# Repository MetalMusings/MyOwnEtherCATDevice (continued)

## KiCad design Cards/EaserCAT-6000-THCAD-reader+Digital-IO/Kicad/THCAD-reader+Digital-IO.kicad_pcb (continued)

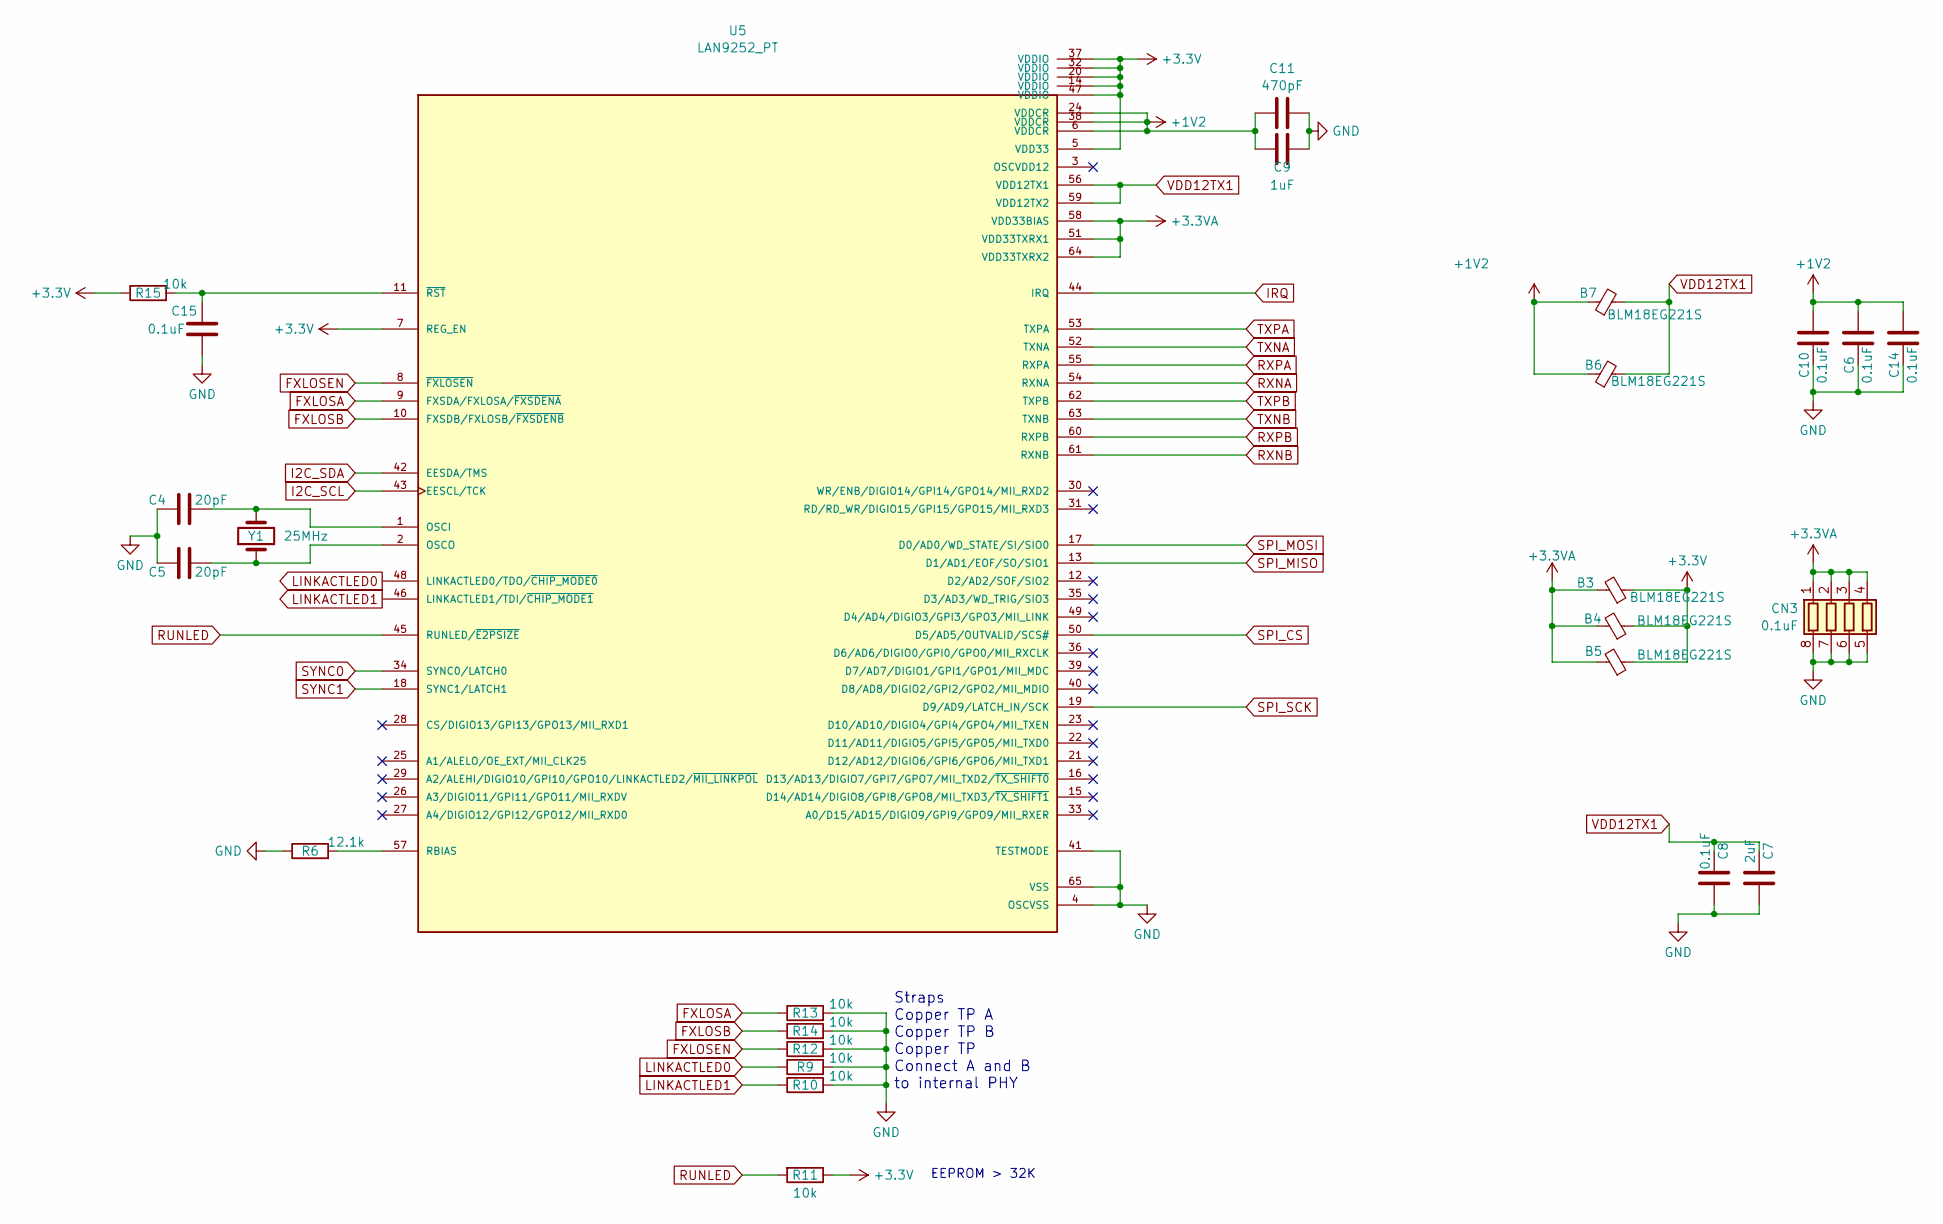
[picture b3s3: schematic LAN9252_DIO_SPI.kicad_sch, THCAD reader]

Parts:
B3, B4, B5, B6, B7: BLM18EG221S; C_0805_2012Metric
C4, C5: 20pF; C_0603_1608Metric
C6, C8, C10, C14, C15: 0.1uF; C_0603_1608Metric
C7: 2uF; C_0603_1608Metric
C9: 1uF; C_0603_1608Metric
C11: 470pF; C_0603_1608Metric
CN3: 0.1uF; R_Array_Convex_4x0603
R6: 12.1k; R_0603_1608Metric
R9, R10, R11, R12, R13, R14, R15: 10k; R_0603_1608Metric
U5: LAN9252_PT; TQFP-64-1EP_10x10mm_P0.5mm_EP8x8mm; PARTREV 04-08-15
Y1: 25MHz; Crystal_HC49-4H_Vertical

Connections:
+1V2: B6.1, B7.1, C6.2, C9.1, C10.2, C11.1, C14.2, U5.6 (VDDCR), U5.24 (VDDCR), U5.38 (VDDCR)
+3.3V: B3.1, B4.1, B5.1, R11.1, R15.1, U5.5 (VDD33), U5.7 (REG_EN), U5.14 (VDDIO), U5.20 (VDDIO), U5.32 (VDDIO), U5.37 (VDDIO), U5.47 (VDDIO); also elsewhere on the board
+3.3VA: B3.2, B4.2, B5.2, CN3.1 (R1.1), CN3.2 (R2.1), CN3.3 (R3.1), CN3.4 (R4.1), U5.51 (VDD33TXRX1), U5.58 (VDD33BIAS), U5.64 (VDD33TXRX2)
FXLOSA: R13.1, U5.9 (FXSDA/FXLOSA/~FXSDENA)
FXLOSB: R14.1, U5.10 (FXSDB/FXLOSB/~FXSDENB)
FXLOSEN: R12.1, U5.8 (~FXLOSEN)
GND: C4.1, C5.1, C6.1, C7.2, C8.2, C9.2, C10.1, C11.2, C14.1, C15.1, CN3.5 (R4.2), CN3.6 (R3.2), CN3.7 (R2.2), CN3.8 (R1.2), R6.1, R9.2, R10.2, R12.2, R13.2, R14.2, U5.4 (OSCVSS), U5.41 (TESTMODE), U5.65 (VSS); also elsewhere on the board
I2C_SCL: U5.43 (EESCL/TCK); also elsewhere on the board
I2C_SDA: U5.42 (EESDA/TMS); also elsewhere on the board
IRQ: U5.44 (IRQ); also elsewhere on the board
LINKACTLED0: R9.1, U5.48 (LINKACTLED0/TDO/~CHIP_MODE0); also elsewhere on the board
LINKACTLED1: R10.1, U5.46 (LINKACTLED1/TDI/~CHIP_MODE1); also elsewhere on the board
unnamed: C4.2, U5.1 (OSCI), Y1.2
unnamed: C5.2, U5.2 (OSCO), Y1.1
unnamed: R6.2, U5.57 (RBIAS)
unnamed: C15.2, R15.2, U5.11 (~RST)
RUNLED: R11.2, U5.45 (RUNLED/~E2PSIZE); also elsewhere on the board
RXNA: U5.54 (RXNA); also elsewhere on the board
RXNB: U5.61 (RXNB); also elsewhere on the board
RXPA: U5.55 (RXPA); also elsewhere on the board
RXPB: U5.60 (RXPB); also elsewhere on the board
SPI_CS: U5.50 (D5/AD5/OUTVALID/SCS#); also elsewhere on the board
SPI_MISO: U5.13 (D1/AD1/EOF/SO/SIO1); also elsewhere on the board
SPI_MOSI: U5.17 (D0/AD0/WD_STATE/SI/SIO0); also elsewhere on the board
SPI_SCK: U5.19 (D9/AD9/LATCH_IN/SCK); also elsewhere on the board
SYNC0: U5.34 (SYNC0/LATCH0); also elsewhere on the board
SYNC1: U5.18 (SYNC1/LATCH1); also elsewhere on the board
TXNA: U5.52 (TXNA); also elsewhere on the board
TXNB: U5.63 (TXNB); also elsewhere on the board
TXPA: U5.53 (TXPA); also elsewhere on the board
TXPB: U5.62 (TXPB); also elsewhere on the board
VDD12TX1: B6.2, B7.2, C7.1, C8.1, U5.56 (VDD12TX1), U5.59 (VDD12TX2)

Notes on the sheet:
Straps Copper TP A Copper TP B Copper TP Connect A and B to internal PHY
EEPROM > 32K

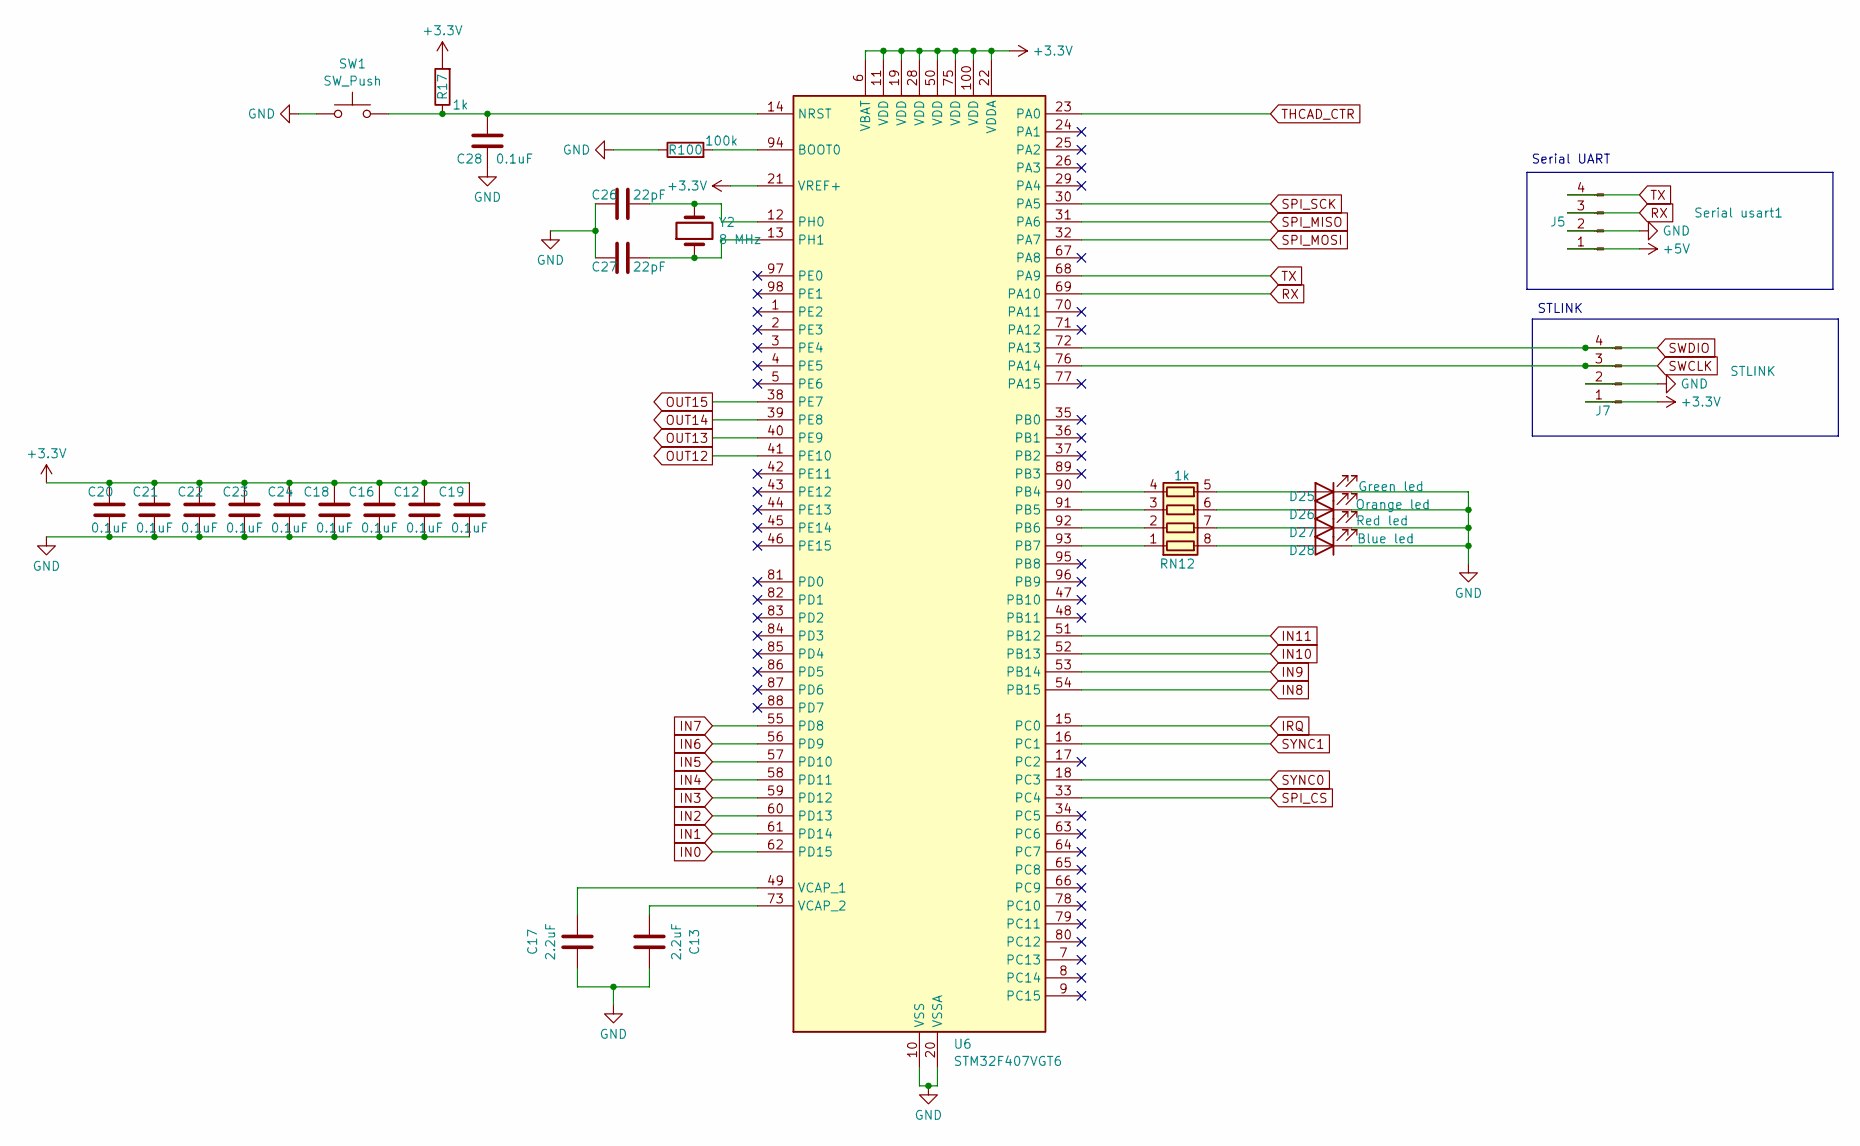
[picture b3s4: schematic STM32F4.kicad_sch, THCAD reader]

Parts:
C12, C16, C18, C19, C20, C21, C22, C23, C24, C28: 0.1uF; C_0603_1608Metric
C13, C17: 2.2uF; C_0603_1608Metric
C26, C27: 22pF; C_0603_1608Metric
D25: Green led; LED_0603_1608Metric
D26: Orange led; LED_0603_1608Metric
D27: Red led; LED_0603_1608Metric
D28: Blue led; LED_0603_1608Metric
J5: Serial usart1; JST_XH_B4B-XH-A_1x04_P2.50mm_Vertical
J7: STLINK; JST_XH_B4B-XH-A_1x04_P2.50mm_Vertical
R17: 1k; R_0603_1608Metric
R100: 100k; R_0603_1608Metric
RN12: 1k; R_Array_Convex_4x0603
SW1: SW_Push; SW_Push_1P1T_XKB_TS-1187A
U6: STM32F407VGT6; LQFP-100_14x14mm_P0.5mm
Y2: 8 MHz; Crystal_HC49-4H_Vertical

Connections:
+3.3V: C12.1, C16.1, C18.1, C19.1, C20.1, C21.1, C22.1, C23.1, C24.1, J7.1, R17.2, U6.6 (VBAT), U6.11 (VDD), U6.19 (VDD), U6.21 (VREF+), U6.22 (VDDA), U6.28 (VDD), U6.50 (VDD), U6.75 (VDD), U6.100 (VDD); also elsewhere on the board
+5V: J5.1; also elsewhere on the board
GND: C12.2, C13.1, C16.2, C17.1, C18.2, C19.2, C20.2, C21.2, C22.2, C23.2, C24.2, C26.1, C27.1, C28.1, D25.1 (K), D26.1 (K), D27.1 (K), D28.1 (K), J5.2, J7.2, R100.1, SW1.1, U6.10 (VSS), U6.20 (VSSA), U6.27 (VSS), U6.74 (VSS), U6.99 (VSS); also elsewhere on the board
IN0: U6.62 (PD15); also elsewhere on the board
IN1: U6.61 (PD14); also elsewhere on the board
IN2: U6.60 (PD13); also elsewhere on the board
IN3: U6.59 (PD12); also elsewhere on the board
IN4: U6.58 (PD11); also elsewhere on the board
IN5: U6.57 (PD10); also elsewhere on the board
IN6: U6.56 (PD9); also elsewhere on the board
IN7: U6.55 (PD8); also elsewhere on the board
IN8: U6.54 (PB15); also elsewhere on the board
IN9: U6.53 (PB14); also elsewhere on the board
IN10: U6.52 (PB13); also elsewhere on the board
IN11: U6.51 (PB12); also elsewhere on the board
IRQ: U6.15 (PC0); also elsewhere on the board
unnamed: D25.2 (A), RN12.5 (R4.2)
unnamed: D26.2 (A), RN12.6 (R3.2)
unnamed: D27.2 (A), RN12.7 (R2.2)
unnamed: D28.2 (A), RN12.8 (R1.2)
unnamed: RN12.1 (R1.1), U6.93 (PB7)
unnamed: RN12.2 (R2.1), U6.92 (PB6)
unnamed: RN12.3 (R3.1), U6.91 (PB5)
unnamed: RN12.4 (R4.1), U6.90 (PB4)
unnamed: R100.2, U6.94 (BOOT0)
unnamed: C28.2, R17.1, SW1.2, U6.14 (NRST)
unnamed: C26.2, U6.12 (PH0), Y2.2
unnamed: C27.2, U6.13 (PH1), Y2.1
unnamed: C17.2, U6.49 (VCAP_1)
unnamed: C13.2, U6.73 (VCAP_2)
OUT12: U6.41 (PE10); also elsewhere on the board
OUT13: U6.40 (PE9); also elsewhere on the board
OUT14: U6.39 (PE8); also elsewhere on the board
OUT15: U6.38 (PE7); also elsewhere on the board
RX: J5.3, U6.69 (PA10)
SPI_CS: U6.33 (PC4); also elsewhere on the board
SPI_MISO: U6.31 (PA6); also elsewhere on the board
SPI_MOSI: U6.32 (PA7); also elsewhere on the board
SPI_SCK: U6.30 (PA5); also elsewhere on the board
SWCLK: J7.3, U6.76 (PA14)
SWDIO: J7.4, U6.72 (PA13)
SYNC0: U6.18 (PC3); also elsewhere on the board
SYNC1: U6.16 (PC1); also elsewhere on the board
THCAD_CTR: U6.23 (PA0); also elsewhere on the board
TX: J5.4, U6.68 (PA9)

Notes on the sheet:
STLINK
Serial UART

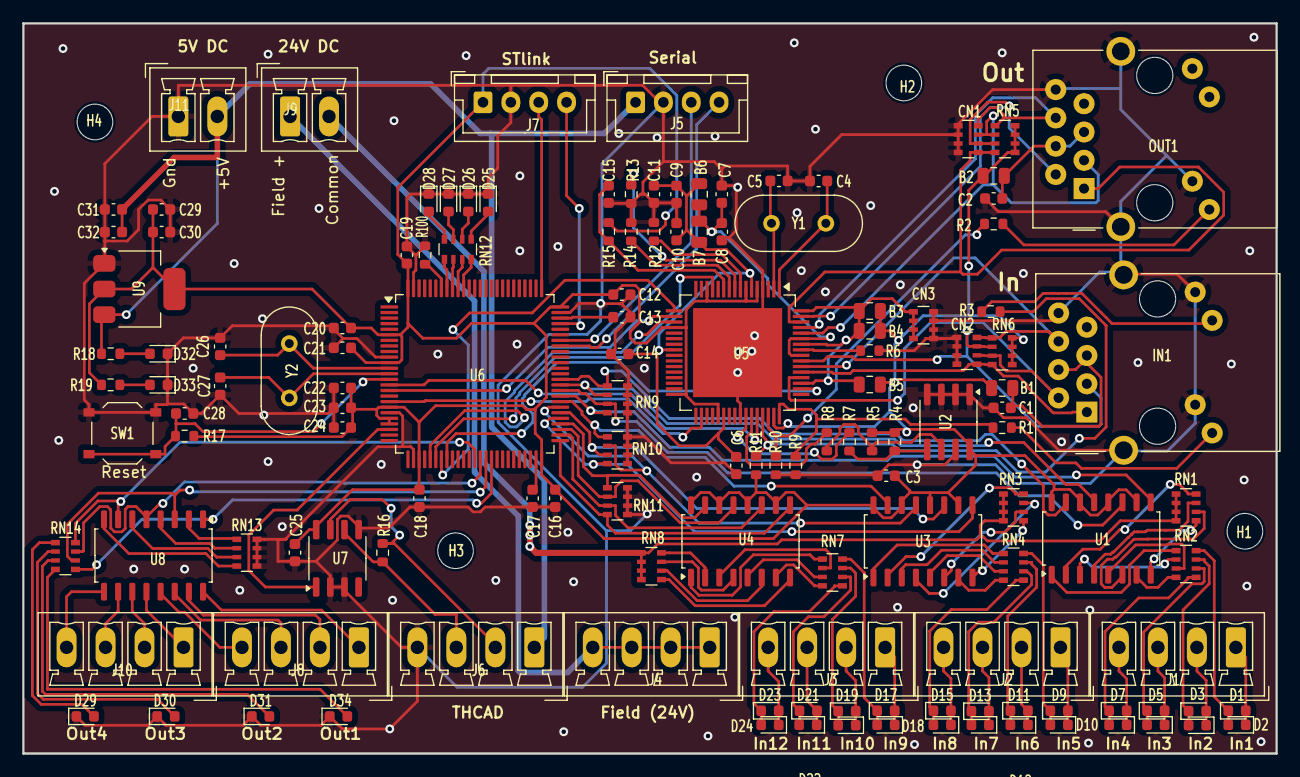
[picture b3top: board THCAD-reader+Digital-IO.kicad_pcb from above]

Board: 2 copper layers, 112.5 x 65.6 mm, 139 parts (0 on the bottom side), 145 nets.

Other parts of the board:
C25: 0.1uF; C_0603_1608Metric
J6: THCAD; PhoenixContact_MCV_1,5_4-G-3.5_1x04_P3.50mm_Vertical
R16: 120; R_0603_1608Metric
U7: MAX3485CSA/ESA; SO-8_3.9x4.9mm_P1.27mm

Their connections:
+3.3V: C25.1, U7.8 (VCC); also elsewhere on the board
+5V: J6.1; also elsewhere on the board
A: J6.2, R16.2, U7.7 (B)
B: J6.3, R16.1, U7.6 (A)
GND: C25.2, J6.4, U7.2 (~RE), U7.3 (DE), U7.5 (GND); also elsewhere on the board
THCAD_CTR: U7.1 (RO); also elsewhere on the board

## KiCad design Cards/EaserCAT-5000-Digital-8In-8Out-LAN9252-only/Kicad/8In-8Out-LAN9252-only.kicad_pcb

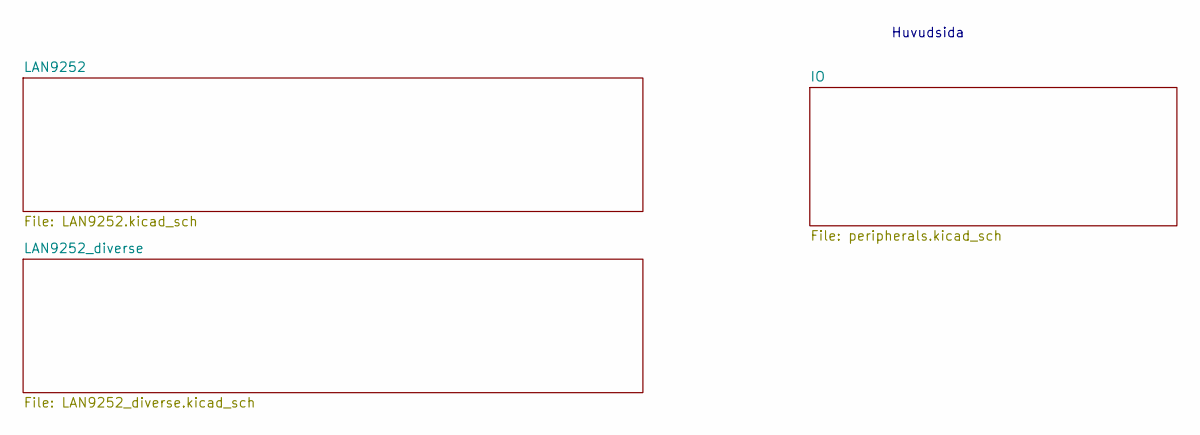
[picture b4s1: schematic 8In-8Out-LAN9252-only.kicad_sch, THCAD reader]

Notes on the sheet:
Huvudsida

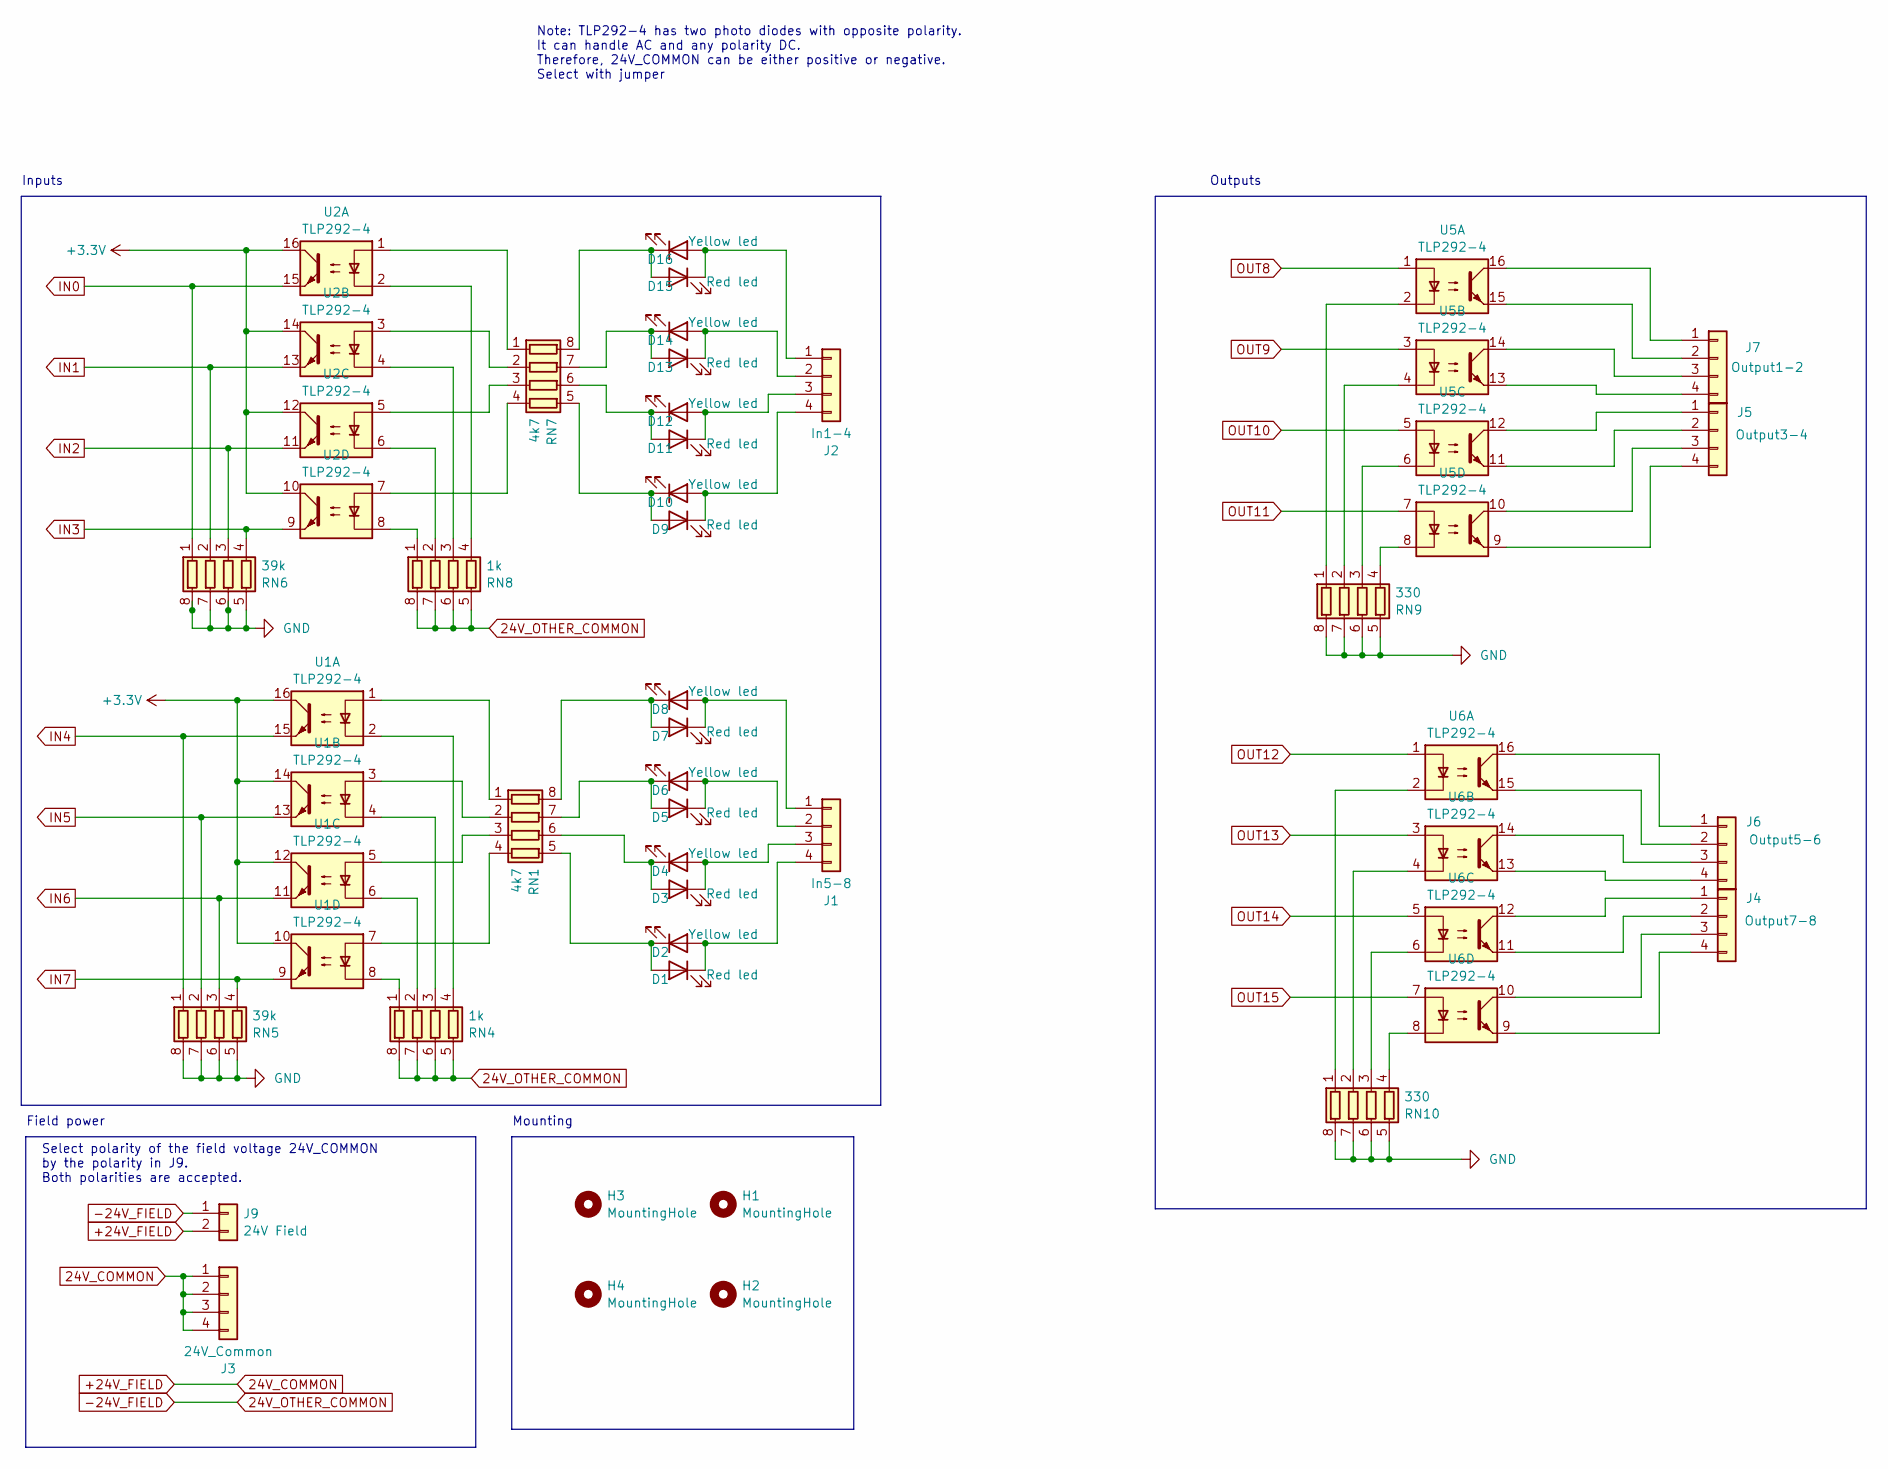
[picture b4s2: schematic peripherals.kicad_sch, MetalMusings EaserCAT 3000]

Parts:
D1, D3, D5, D7, D9, D11, D13, D15: Red led; LED_0603_1608Metric
D2, D4, D6, D8, D10, D12, D14, D16: Yellow led; LED_0603_1608Metric
H1, H2, H3, H4: MountingHole; MountingHole_3.2mm_M3_ISO14580
J1: In5-8; PhoenixContact_MCV_1,5_4-G-3.5_1x04_P3.50mm_Vertical
J2: In1-4; PhoenixContact_MCV_1,5_4-G-3.5_1x04_P3.50mm_Vertical
J3: 24V_Common; PhoenixContact_MCV_1,5_4-G-3.5_1x04_P3.50mm_Vertical
J4: Output7-8; PhoenixContact_MCV_1,5_4-G-3.5_1x04_P3.50mm_Vertical
J5: Output3-4; PhoenixContact_MCV_1,5_4-G-3.5_1x04_P3.50mm_Vertical
J6: Output5-6; PhoenixContact_MCV_1,5_4-G-3.5_1x04_P3.50mm_Vertical
J7: Output1-2; PhoenixContact_MCV_1,5_4-G-3.5_1x04_P3.50mm_Vertical
J9: 24V Field; PhoenixContact_MCV_1,5_2-G-3.5_1x02_P3.50mm_Vertical
RN1, RN7: 4k7; R_Array_Convex_4x0603
RN4, RN8: 1k; R_Array_Convex_4x0603
RN5, RN6: 39k; R_Array_Convex_4x0603
RN9, RN10: 330; R_Array_Convex_4x0603
U1, U2, U5, U6: TLP292-4; SOIC-16_4.55x10.3mm_P1.27mm

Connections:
+3.3V: U1.10, U1.12, U1.14, U1.16, U2.10, U2.12, U2.14, U2.16; also elsewhere on the board
+24V_FIELD: J3.1, J3.2, J3.3, J3.4, J9.2
-24V_FIELD: J9.1, RN4.5 (R4.2), RN4.6 (R3.2), RN4.7 (R2.2), RN4.8 (R1.2), RN8.5 (R4.2), RN8.6 (R3.2), RN8.7 (R2.2), RN8.8 (R1.2)
GND: RN5.5 (R4.2), RN5.6 (R3.2), RN5.7 (R2.2), RN5.8 (R1.2), RN6.5 (R4.2), RN6.6 (R3.2), RN6.7 (R2.2), RN6.8 (R1.2), RN9.5 (R4.2), RN9.6 (R3.2), RN9.7 (R2.2), RN9.8 (R1.2), RN10.5 (R4.2), RN10.6 (R3.2), RN10.7 (R2.2), RN10.8 (R1.2); also elsewhere on the board
IN0: RN6.1 (R1.1), U2.15; also elsewhere on the board
IN1: RN6.2 (R2.1), U2.13; also elsewhere on the board
IN2: RN6.3 (R3.1), U2.11; also elsewhere on the board
IN3: RN6.4 (R4.1), U2.9; also elsewhere on the board
IN4: RN5.1 (R1.1), U1.15; also elsewhere on the board
IN5: RN5.2 (R2.1), U1.13; also elsewhere on the board
IN6: RN5.3 (R3.1), U1.11; also elsewhere on the board
IN7: RN5.4 (R4.1), U1.9; also elsewhere on the board
unnamed: D1.2 (A), D2.1 (K), RN1.5 (R4.2)
unnamed: D1.1 (K), D2.2 (A), J1.4
unnamed: D3.2 (A), D4.1 (K), RN1.6 (R3.2)
unnamed: D3.1 (K), D4.2 (A), J1.3
unnamed: D5.2 (A), D6.1 (K), RN1.7 (R2.2)
unnamed: D5.1 (K), D6.2 (A), J1.2
unnamed: D7.2 (A), D8.1 (K), RN1.8 (R1.2)
unnamed: D7.1 (K), D8.2 (A), J1.1
unnamed: D9.1 (K), D10.2 (A), J2.4
unnamed: D9.2 (A), D10.1 (K), RN7.5 (R4.2)
unnamed: D11.2 (A), D12.1 (K), RN7.6 (R3.2)
unnamed: D11.1 (K), D12.2 (A), J2.3
unnamed: D13.2 (A), D14.1 (K), RN7.7 (R2.2)
unnamed: D13.1 (K), D14.2 (A), J2.2
unnamed: D15.2 (A), D16.1 (K), RN7.8 (R1.2)
unnamed: D15.1 (K), D16.2 (A), J2.1
unnamed: J4.1, U6.12
unnamed: J4.2, U6.11
unnamed: J4.3, U6.10
unnamed: J4.4, U6.9
unnamed: J5.1, U5.12
unnamed: J5.2, U5.11
unnamed: J5.3, U5.10
unnamed: J5.4, U5.9
unnamed: J6.1, U6.16
unnamed: J6.2, U6.15
unnamed: J6.3, U6.14
unnamed: J6.4, U6.13
unnamed: J7.1, U5.16
unnamed: J7.2, U5.15
unnamed: J7.3, U5.14
unnamed: J7.4, U5.13
unnamed: RN1.1 (R1.1), U1.1
unnamed: RN1.2 (R2.1), U1.3
unnamed: RN1.3 (R3.1), U1.5
unnamed: RN1.4 (R4.1), U1.7
unnamed: RN4.1 (R1.1), U1.8
unnamed: RN4.2 (R2.1), U1.6
unnamed: RN4.3 (R3.1), U1.4
unnamed: RN4.4 (R4.1), U1.2
unnamed: RN7.1 (R1.1), U2.1
unnamed: RN7.2 (R2.1), U2.3
unnamed: RN7.3 (R3.1), U2.5
unnamed: RN7.4 (R4.1), U2.7
unnamed: RN8.1 (R1.1), U2.8
unnamed: RN8.2 (R2.1), U2.6
unnamed: RN8.3 (R3.1), U2.4
unnamed: RN8.4 (R4.1), U2.2
unnamed: RN9.1 (R1.1), U5.2
unnamed: RN9.2 (R2.1), U5.4
unnamed: RN9.3 (R3.1), U5.6
unnamed: RN9.4 (R4.1), U5.8
unnamed: RN10.1 (R1.1), U6.2
unnamed: RN10.2 (R2.1), U6.4
unnamed: RN10.3 (R3.1), U6.6
unnamed: RN10.4 (R4.1), U6.8
OUT8: U5.1; also elsewhere on the board
OUT9: U5.3; also elsewhere on the board
OUT10: U5.5; also elsewhere on the board
OUT11: U5.7; also elsewhere on the board
OUT12: U6.1; also elsewhere on the board
OUT13: U6.3; also elsewhere on the board
OUT14: U6.5; also elsewhere on the board
OUT15: U6.7; also elsewhere on the board

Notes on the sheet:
Inputs
Select polarity of the field voltage 24V_COMMON by the polarity in J9. Both polarities are accepted.
Mounting
Outputs
Field power
Note: TLP292-4 has two photo diodes with opposite polarity. It can handle AC and any polarity DC. Therefore, 24V_COMMON can be either positive or negative. Select with jumper

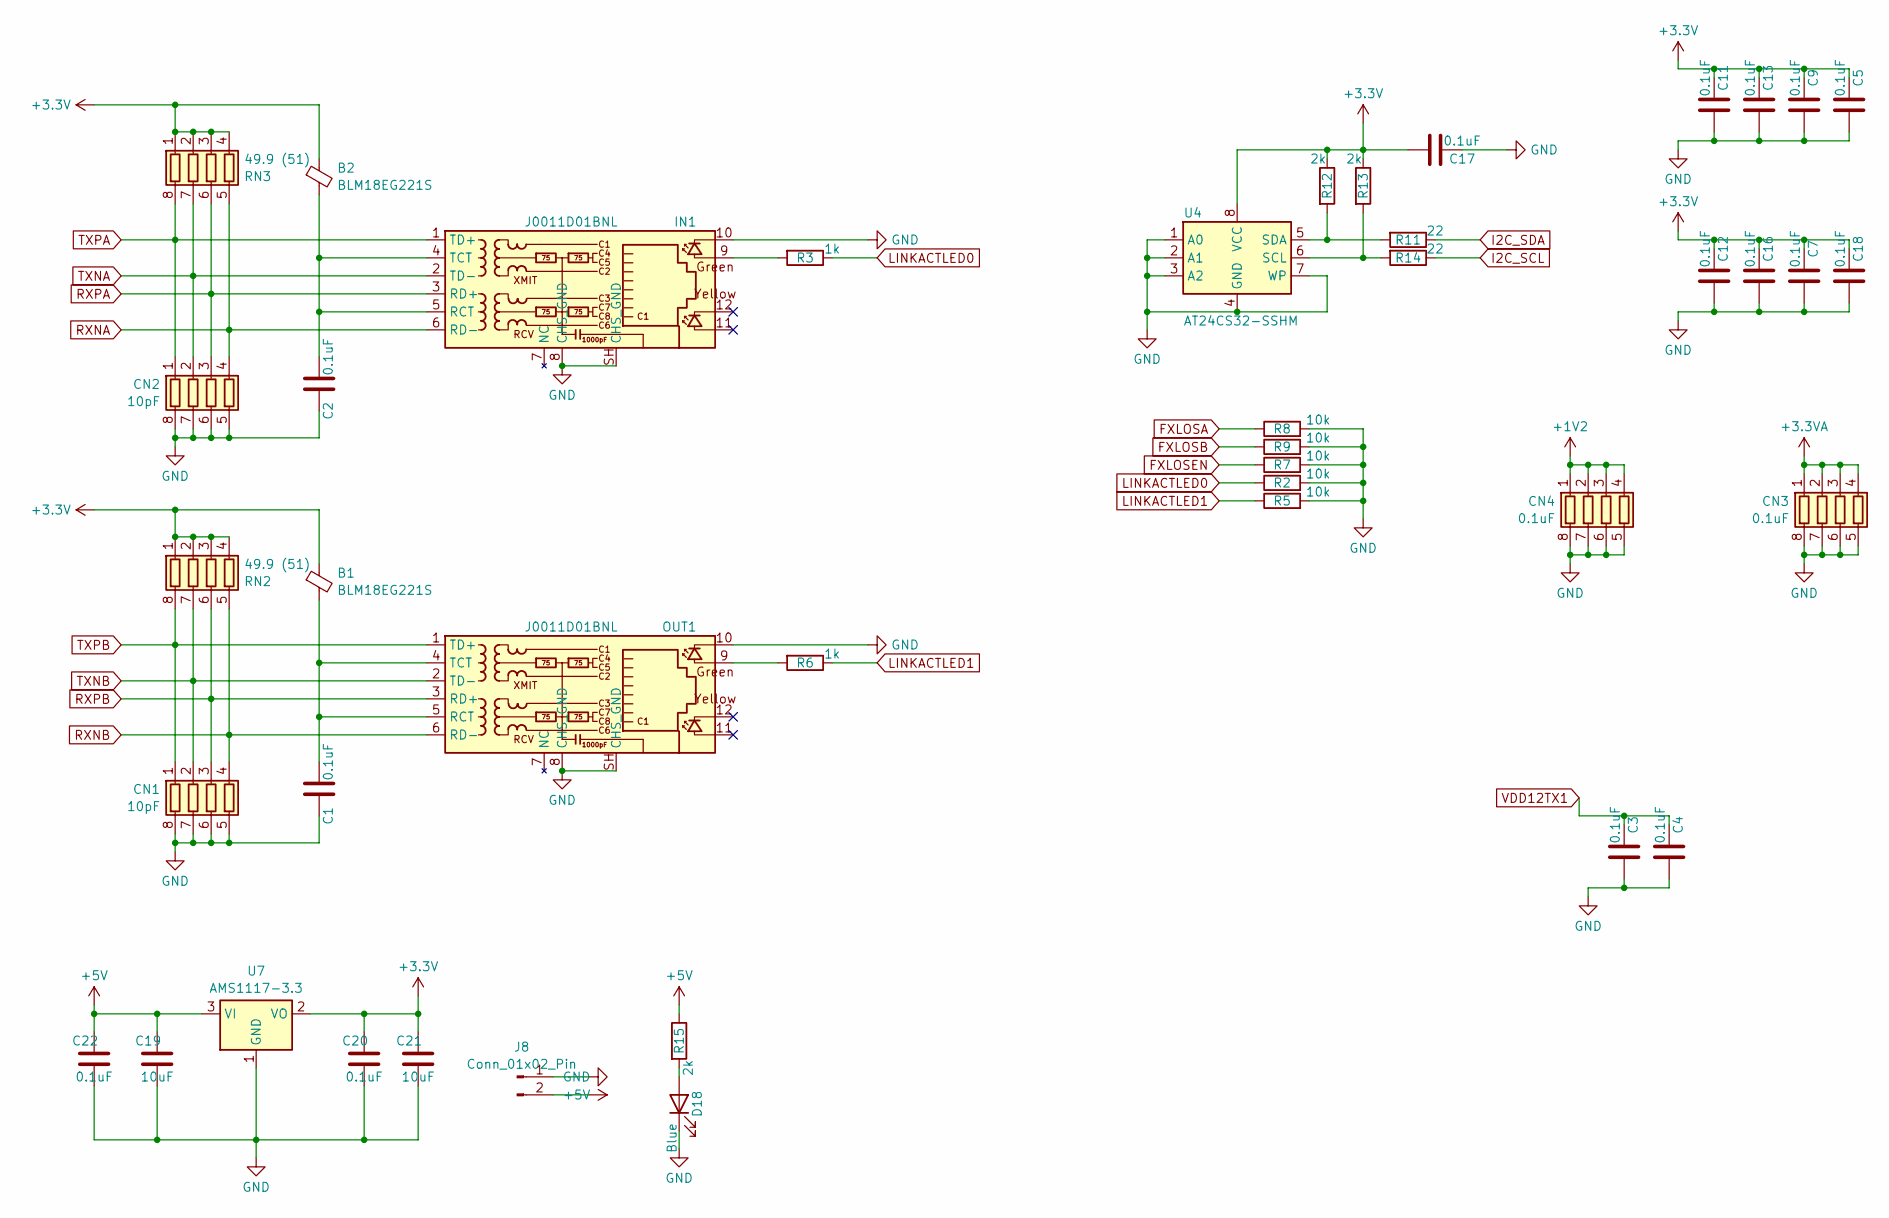
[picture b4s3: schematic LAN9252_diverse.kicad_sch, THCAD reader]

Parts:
B1, B2: BLM18EG221S; C_0805_2012Metric
C1, C2, C3, C4, C5, C7, C9, C11, C12, C13, C16, C17, C18, C20, C22: 0.1uF; C_0805_2012Metric
C19, C21: 10uF; C_0805_2012Metric
CN1, CN2: 10pF; R_Array_Convex_4x0603
CN3, CN4: 0.1uF; R_Array_Convex_4x0603
D18: Blue; LED_0805_2012Metric
IN1: J0011D01BNL; PulseJack JB0011D01BNL
J8: Conn_01x02_Pin; JST_XH_B2B-XH-A_1x02_P2.50mm_Vertical
OUT1: J0011D01BNL; PulseJack JB0011D01BNL
R2, R5, R7, R8, R9: 10k; R_0805_2012Metric
R3, R6: 1k; R_0805_2012Metric
R11, R14: 22; R_0805_2012Metric
R12, R13, R15: 2k; R_0805_2012Metric
RN2, RN3: 49.9 (51); R_Array_Convex_4x0603
U4: AT24CS32-SSHM; SOIC-8_3.9x4.9mm_P1.27mm
U7: AMS1117-3.3; SOT-223-3_TabPin2

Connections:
+1V2: CN4.1 (R1.1), CN4.2 (R2.1), CN4.3 (R3.1), CN4.4 (R4.1); also elsewhere on the board
+3.3V: B1.1, B2.1, C5.1, C7.1, C9.1, C11.1, C12.1, C13.1, C16.1, C17.2, C18.1, C20.1, C21.1, R12.1, R13.1, RN2.1 (R1.1), RN2.2 (R2.1), RN2.3 (R3.1), RN2.4 (R4.1), RN3.1 (R1.1), RN3.2 (R2.1), RN3.3 (R3.1), RN3.4 (R4.1), U4.8 (VCC), U7.2 (VO); also elsewhere on the board
+3.3VA: CN3.1 (R1.1), CN3.2 (R2.1), CN3.3 (R3.1), CN3.4 (R4.1); also elsewhere on the board
+5V: C19.1, C22.1, J8.2, R15.1, U7.3 (VI)
FXLOSA: R8.1; also elsewhere on the board
FXLOSB: R9.1; also elsewhere on the board
FXLOSEN: R7.1; also elsewhere on the board
GND: C1.1, C2.1, C3.2, C4.2, C5.2, C7.2, C9.2, C11.2, C12.2, C13.2, C16.2, C17.1, C18.2, C19.2, C20.2, C21.2, C22.2, CN1.5 (R4.2), CN1.6 (R3.2), CN1.7 (R2.2), CN1.8 (R1.2), CN2.5 (R4.2), CN2.6 (R3.2), CN2.7 (R2.2), CN2.8 (R1.2), CN3.5 (R4.2), CN3.6 (R3.2), CN3.7 (R2.2), CN3.8 (R1.2), CN4.5 (R4.2), CN4.6 (R3.2), CN4.7 (R2.2), CN4.8 (R1.2), D18.1 (K), IN1.8 (CHS_GND), IN1.10, IN1.SH (CHS_GND), J8.1, OUT1.8 (CHS_GND), OUT1.10, OUT1.SH (CHS_GND), R2.2, R5.2, R7.2, R8.2, R9.2, U4.1 (A0), U4.2 (A1), U4.3 (A2), U4.4 (GND), U4.7 (WP), U7.1 (GND); also elsewhere on the board
I2C_SCL: R14.1; also elsewhere on the board
I2C_SDA: R11.1; also elsewhere on the board
LINKACTLED0: R2.1, R3.1; also elsewhere on the board
LINKACTLED1: R5.1, R6.1; also elsewhere on the board
unnamed: D18.2 (A), R15.2
unnamed: IN1.9, R3.2
unnamed: B2.2, C2.2, IN1.4 (TCT), IN1.5 (RCT)
unnamed: OUT1.9, R6.2
unnamed: B1.2, C1.2, OUT1.4 (TCT), OUT1.5 (RCT)
unnamed: R13.2, R14.2, U4.6 (SCL)
unnamed: R11.2, R12.2, U4.5 (SDA)
RXNA: CN2.4 (R4.1), IN1.6 (RD-), RN3.5 (R4.2); also elsewhere on the board
RXNB: CN1.4 (R4.1), OUT1.6 (RD-), RN2.5 (R4.2); also elsewhere on the board
RXPA: CN2.3 (R3.1), IN1.3 (RD+), RN3.6 (R3.2); also elsewhere on the board
RXPB: CN1.3 (R3.1), OUT1.3 (RD+), RN2.6 (R3.2); also elsewhere on the board
TXNA: CN2.2 (R2.1), IN1.2 (TD-), RN3.7 (R2.2); also elsewhere on the board
TXNB: CN1.2 (R2.1), OUT1.2 (TD-), RN2.7 (R2.2); also elsewhere on the board
TXPA: CN2.1 (R1.1), IN1.1 (TD+), RN3.8 (R1.2); also elsewhere on the board
TXPB: CN1.1 (R1.1), OUT1.1 (TD+), RN2.8 (R1.2); also elsewhere on the board
VDD12TX1: C3.1, C4.1; also elsewhere on the board

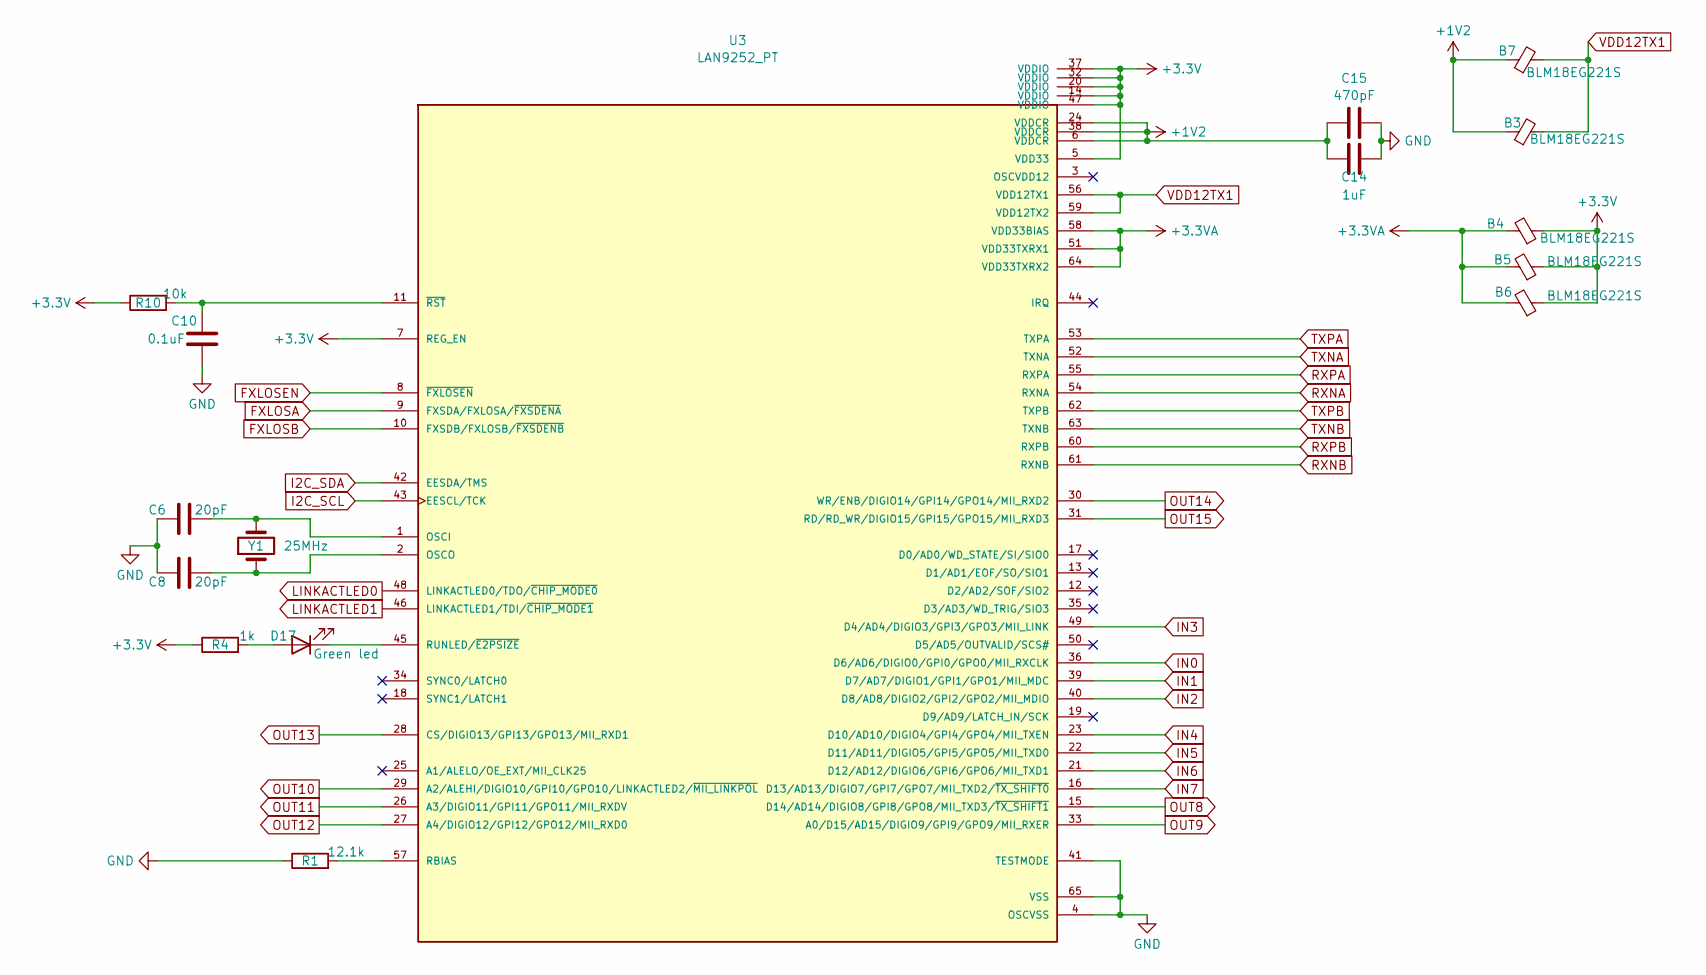
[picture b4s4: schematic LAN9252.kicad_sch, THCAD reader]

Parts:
B3, B4, B5, B6, B7: BLM18EG221S; C_0805_2012Metric
C6, C8: 20pF; C_0805_2012Metric
C10: 0.1uF; C_0805_2012Metric
C14: 1uF; C_0805_2012Metric
C15: 470pF; C_0805_2012Metric
D17: Green led; LED_0805_2012Metric
R1: 12.1k; R_0805_2012Metric
R4: 1k; R_0805_2012Metric
R10: 10k; R_0805_2012Metric
U3: LAN9252_PT; TQFP-64-1EP_10x10mm_P0.5mm_EP8x8mm; PARTREV 04-08-15
Y1: 25MHz; Crystal_HC49-4H_Vertical

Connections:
+1V2: B3.1, B7.1, C14.1, C15.1, U3.6 (VDDCR), U3.24 (VDDCR), U3.38 (VDDCR); also elsewhere on the board
+3.3V: B4.1, B5.1, B6.1, R4.1, R10.1, U3.5 (VDD33), U3.7 (REG_EN), U3.14 (VDDIO), U3.20 (VDDIO), U3.32 (VDDIO), U3.37 (VDDIO), U3.47 (VDDIO); also elsewhere on the board
+3.3VA: B4.2, B5.2, B6.2, U3.51 (VDD33TXRX1), U3.58 (VDD33BIAS), U3.64 (VDD33TXRX2); also elsewhere on the board
FXLOSA: U3.9 (FXSDA/FXLOSA/~FXSDENA); also elsewhere on the board
FXLOSB: U3.10 (FXSDB/FXLOSB/~FXSDENB); also elsewhere on the board
FXLOSEN: U3.8 (~FXLOSEN); also elsewhere on the board
GND: C6.1, C8.1, C10.1, C14.2, C15.2, R1.1, U3.4 (OSCVSS), U3.41 (TESTMODE), U3.65 (VSS); also elsewhere on the board
I2C_SCL: U3.43 (EESCL/TCK); also elsewhere on the board
I2C_SDA: U3.42 (EESDA/TMS); also elsewhere on the board
IN0: U3.36 (D6/AD6/DIGIO0/GPI0/GPO0/MII_RXCLK); also elsewhere on the board
IN1: U3.39 (D7/AD7/DIGIO1/GPI1/GPO1/MII_MDC); also elsewhere on the board
IN2: U3.40 (D8/AD8/DIGIO2/GPI2/GPO2/MII_MDIO); also elsewhere on the board
IN3: U3.49 (D4/AD4/DIGIO3/GPI3/GPO3/MII_LINK); also elsewhere on the board
IN4: U3.23 (D10/AD10/DIGIO4/GPI4/GPO4/MII_TXEN); also elsewhere on the board
IN5: U3.22 (D11/AD11/DIGIO5/GPI5/GPO5/MII_TXD0); also elsewhere on the board
IN6: U3.21 (D12/AD12/DIGIO6/GPI6/GPO6/MII_TXD1); also elsewhere on the board
IN7: U3.16 (D13/AD13/DIGIO7/GPI7/GPO7/MII_TXD2/~TX_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); also elsewhere on the board
LINKACTLED0: U3.48 (LINKACTLED0/TDO/~CHIP_MODE0); also elsewhere on the board
LINKACTLED1: U3.46 (LINKACTLED1/TDI/~CHIP_MODE1); also elsewhere on the board
unnamed: D17.2 (A), R4.2
unnamed: D17.1 (K), U3.45 (RUNLED/~E2PSIZE)
unnamed: C6.2, U3.1 (OSCI), Y1.2
unnamed: C8.2, U3.2 (OSCO), Y1.1
unnamed: R1.2, U3.57 (RBIAS)
unnamed: C10.2, R10.2, U3.11 (~RST)
OUT8: U3.15 (D14/AD14/DIGIO8/GPI8/GPO8/MII_TXD3/~TX_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); also elsewhere on the board
OUT9: U3.33 (A0/D15/AD15/DIGIO9/GPI9/GPO9/MII_RXER); also elsewhere on the board
OUT10: U3.29 (A2/ALEHI/DIGIO10/GPI10/GPO10/LINKACTLED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); also elsewhere on the board
OUT11: U3.26 (A3/DIGIO11/GPI11/GPO11/MII_RXDV); also elsewhere on the board
OUT12: U3.27 (A4/DIGIO12/GPI12/GPO12/MII_RXD0); also elsewhere on the board
OUT13: U3.28 (CS/DIGIO13/GPI13/GPO13/MII_RXD1); also elsewhere on the board
OUT14: U3.30 (WR/ENB/DIGIO14/GPI14/GPO14/MII_RXD2); also elsewhere on the board
OUT15: U3.31 (RD/RD_WR/DIGIO15/GPI15/GPO15/MII_RXD3); also elsewhere on the board
RXNA: U3.54 (RXNA); also elsewhere on the board
RXNB: U3.61 (RXNB); also elsewhere on the board
RXPA: U3.55 (RXPA); also elsewhere on the board
RXPB: U3.60 (RXPB); also elsewhere on the board
TXNA: U3.52 (TXNA); also elsewhere on the board
TXNB: U3.63 (TXNB); also elsewhere on the board
TXPA: U3.53 (TXPA); also elsewhere on the board
TXPB: U3.62 (TXPB); also elsewhere on the board
VDD12TX1: B3.2, B7.2, U3.56 (VDD12TX1), U3.59 (VDD12TX2); also elsewhere on the board
